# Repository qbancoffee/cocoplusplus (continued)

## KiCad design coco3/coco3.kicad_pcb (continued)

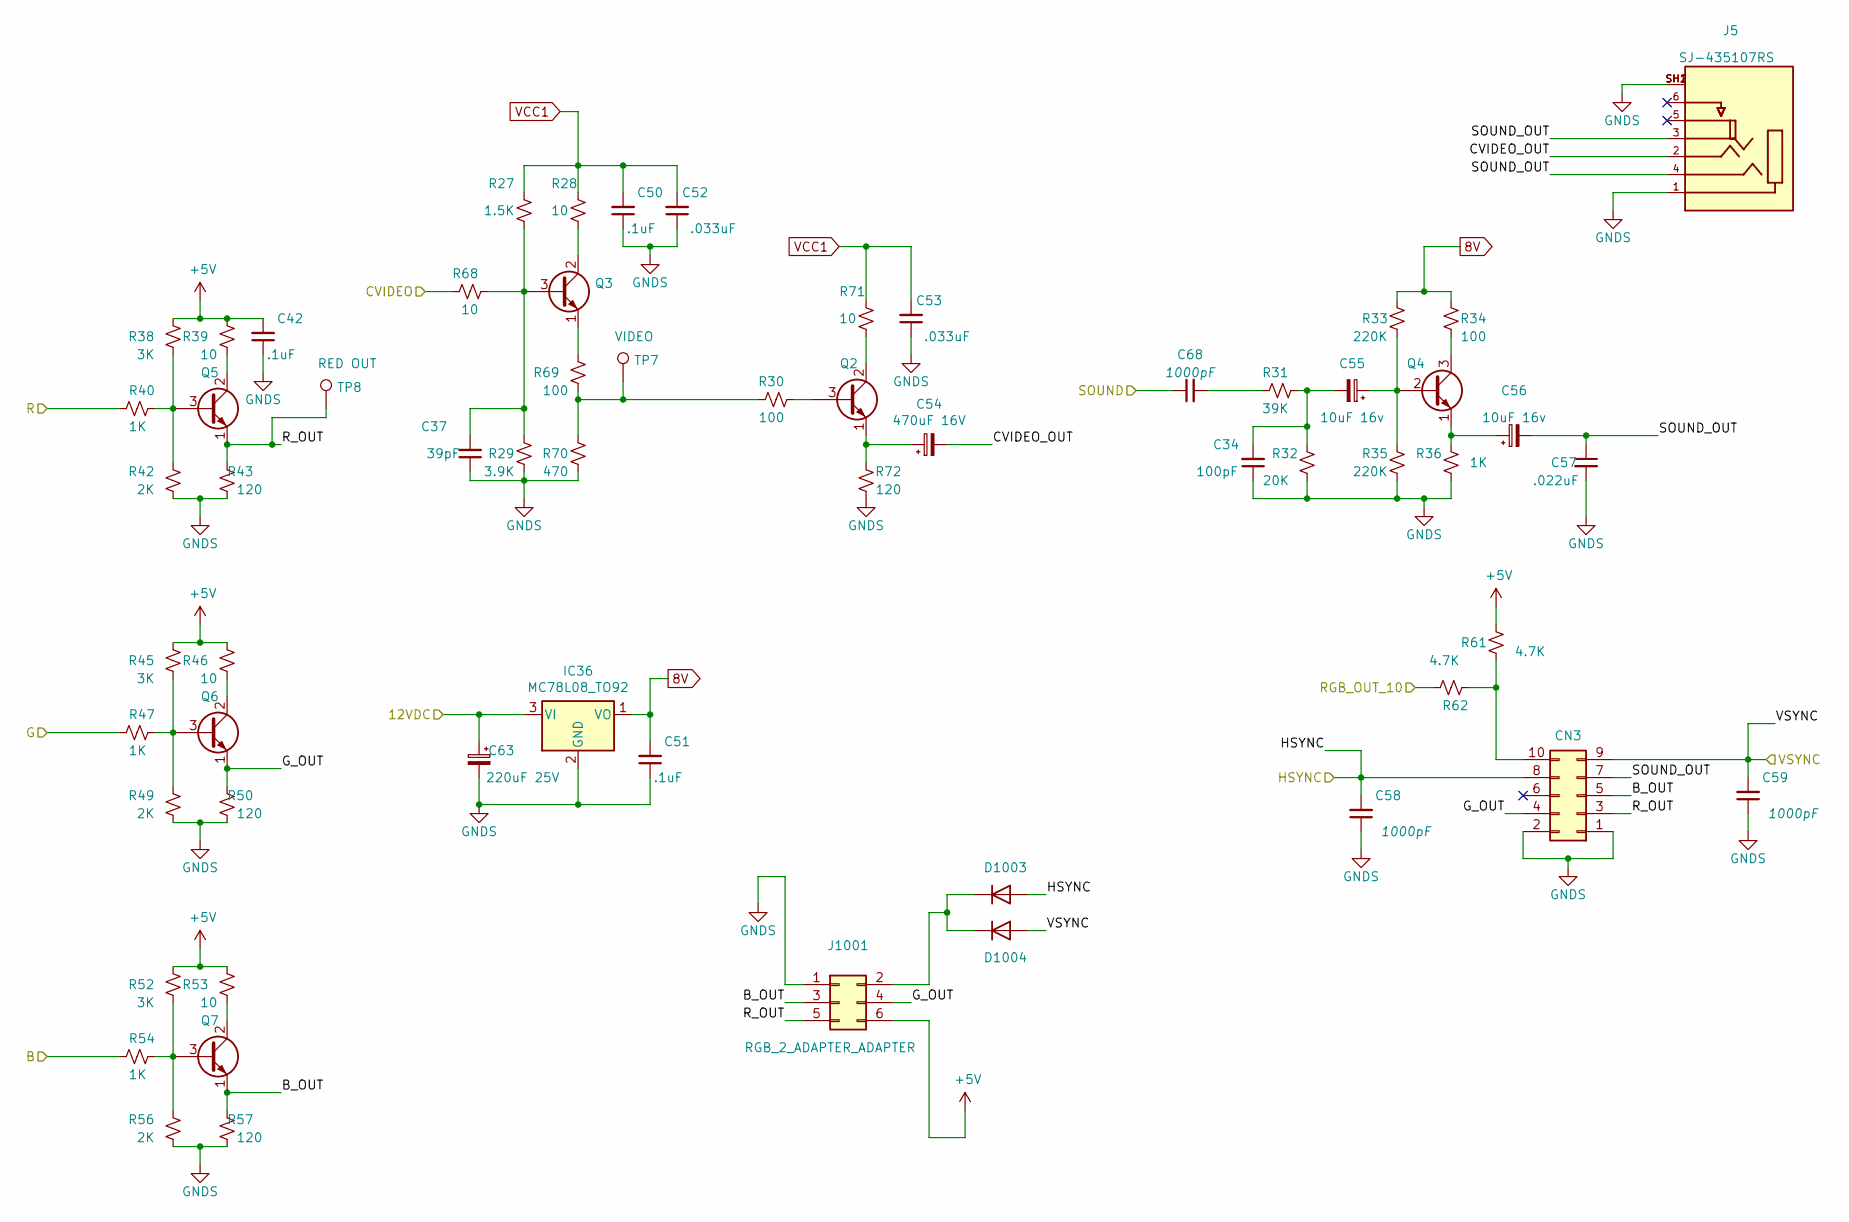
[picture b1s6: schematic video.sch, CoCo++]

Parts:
C34: 100pF; C_0805_2012Metric_Pad1.18x1.45mm_HandSolder; Manufacturer part# CL21C101JBANNNC
C37: 39pF; C_0805_2012Metric_Pad1.18x1.45mm_HandSolder; Manufacturer part# 0805N390J500CT
C42, C50, C51: .1uF; C_0805_2012Metric_Pad1.18x1.45mm_HandSolder; Manufacturer part# CL21A106KAYNNNE
C52, C53: .033uF; C_0805_2012Metric_Pad1.18x1.45mm_HandSolder; Manufacturer part# 0805B333K500NT
C54: 470uF 16V; CP_Elec_8x10; Manufacturer part# VEJ471M1CTR-0810
C55, C56: 10uF 16v; CP_EIA-3216-18_Kemet-A; Manufacturer part# TAJA106K016RNJ
C57: .022uF; C_0805_2012Metric_Pad1.18x1.45mm_HandSolder; Manufacturer part# CL21B223KBANNNC
C58, C59, C68: 1000pF; C_0805_2012Metric_Pad1.18x1.45mm_HandSolder; Manufacturer part# CL21B102KBCNNNC
C63: 220uF 25V; CP_Elec_8x10; Manufacturer part# VEJ221M1ETR-0810
CN3: Conn_02x05_Odd_Even; PinHeader_2x05_P2.54mm_Vertical; Manufacturer part# PRPC005DAAN-RC
D1003, D1004: 1N4148; D_SOD-323F; Manufacturer part# 1N4148WS
IC36: MC78L08_TO92; TO-92_Inline; Manufacturer part# UA78L08ACLPRE3
J5: SJ-435107RS; CUI_SJ-435107RS
J1001: RGB_2_ADAPTER_ADAPTER; PinHeader_2x03_P2.54mm_Horizontal; Manufacturer part# 75867-131LF
Q2, Q3, Q5, Q6, Q7: 2SC945(NTE85); TO-92L_Inline; Manufacturer part# NTE85
Q4: MPSA13(NTE46); TO-92L_Inline; Manufacturer part# NTE46
R27: 1.5K; R_1206_3216Metric_Pad1.30x1.75mm_HandSolder; Manufacturer part# UNI-ROYAL(Uniroyal Elec)
R28, R39, R46, R53, R68, R71: 10; R_1206_3216Metric_Pad1.30x1.75mm_HandSolder; Manufacturer part# 1206W4F100JT5E
R29: 3.9K; R_1206_3216Metric_Pad1.30x1.75mm_HandSolder; Manufacturer part# 1206W4F3901T5E
R30, R34, R69: 100; R_1206_3216Metric_Pad1.30x1.75mm_HandSolder; Manufacturer part# 1206W4F1000T5E
R31: 39K; R_1206_3216Metric_Pad1.30x1.75mm_HandSolder; Manufacturer part# 1206W4F3902T5E
R32: 20K; R_1206_3216Metric_Pad1.30x1.75mm_HandSolder; Manufacturer part# 1206W4F620KT5E
R33, R35: 220K; R_1206_3216Metric_Pad1.30x1.75mm_HandSolder; Manufacturer part# 1206W4F2203T5E
R36, R40, R47, R54: 1K; R_1206_3216Metric_Pad1.30x1.75mm_HandSolder; Manufacturer part# 1206W4F1001T5
R38, R45, R52: 3K; R_1206_3216Metric_Pad1.30x1.75mm_HandSolder; Manufacturer part# 1206W4F3001T5E
R42, R49, R56: 2K; R_1206_3216Metric_Pad1.30x1.75mm_HandSolder; Manufacturer part# 1206W4F2001T5E
R43, R50, R57, R72: 120; R_1206_3216Metric_Pad1.30x1.75mm_HandSolder; Manufacturer part# 1206W4F1200T5E
R61, R62: 4.7K; R_1206_3216Metric_Pad1.30x1.75mm_HandSolder; Manufacturer part# 1206W4F4701T5E
R70: 470; R_1206_3216Metric_Pad1.30x1.75mm_HandSolder; Manufacturer part# 1206W4J0471T5E
TP7: VIDEO; TestPoint_Pad_3.0x3.0mm
TP8: RED OUT; TestPoint_Pad_3.0x3.0mm

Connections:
8V: C51.2, IC36.1 (VO), R33.1, R34.2
+5V: C42.2, J1001.6, R38.2, R39.2, R45.2, R46.2, R52.2, R53.2, R61.1; also elsewhere on the board
/gime/B: R54.2; also elsewhere on the board
/gime/CVIDEO: R68.1; also elsewhere on the board
/gime/G: R47.2; also elsewhere on the board
/gime/HSYNC: C58.2, CN3.8, D1003.2 (A); also elsewhere on the board
/gime/R: R40.2; also elsewhere on the board
/gime/VSYNC: C59.2, CN3.9, D1004.2 (A); also elsewhere on the board
/peripherals/RGB_OUT_10: R62.1; also elsewhere on the board
/peripherals/SOUND: C68.1; also elsewhere on the board
/power/12VDC: C63.1, IC36.3 (VI); also elsewhere on the board
/video/B_OUT: CN3.5, J1001.3, Q7.1 (E), R57.2
/video/CVIDEO_OUT: C54.2, J5.2
/video/G_OUT: CN3.4, J1001.4, Q6.1 (E), R50.2
/video/R_OUT: CN3.3, J1001.5, Q5.1 (E), R43.2, TP8.1
/video/SOUND_OUT: C56.2, C57.1, CN3.7, J5.3, J5.4
unnamed: C34.2, C55.2, R31.2, R32.1
unnamed: C37.2, Q3.3 (B), R27.1, R29.2, R68.2
unnamed: C54.1, Q2.1 (E), R72.2
unnamed: C55.1, Q4.2 (B), R33.2, R35.1
unnamed: C56.1, Q4.1 (E), R36.1
unnamed: C68.2, R31.1
unnamed: CN3.10, R61.2, R62.2
unnamed: D1003.1 (K), D1004.1 (K), J1001.2
unnamed: Q2.2 (C), R71.1
unnamed: Q2.3 (B), R30.2
unnamed: Q3.1 (E), R69.2
unnamed: Q3.2 (C), R28.1
unnamed: Q4.3 (C), R34.1
unnamed: Q5.2 (C), R39.1
unnamed: Q5.3 (B), R38.1, R40.1, R42.2
unnamed: Q6.2 (C), R46.1
unnamed: Q6.3 (B), R45.1, R47.1, R49.2
unnamed: Q7.2 (C), R53.1
unnamed: Q7.3 (B), R52.1, R54.1, R56.2
unnamed: R30.1, R69.1, R70.2, TP7.1
VCC1: C50.2, C52.2, C53.2, R27.2, R28.2, R71.2; also elsewhere on the board

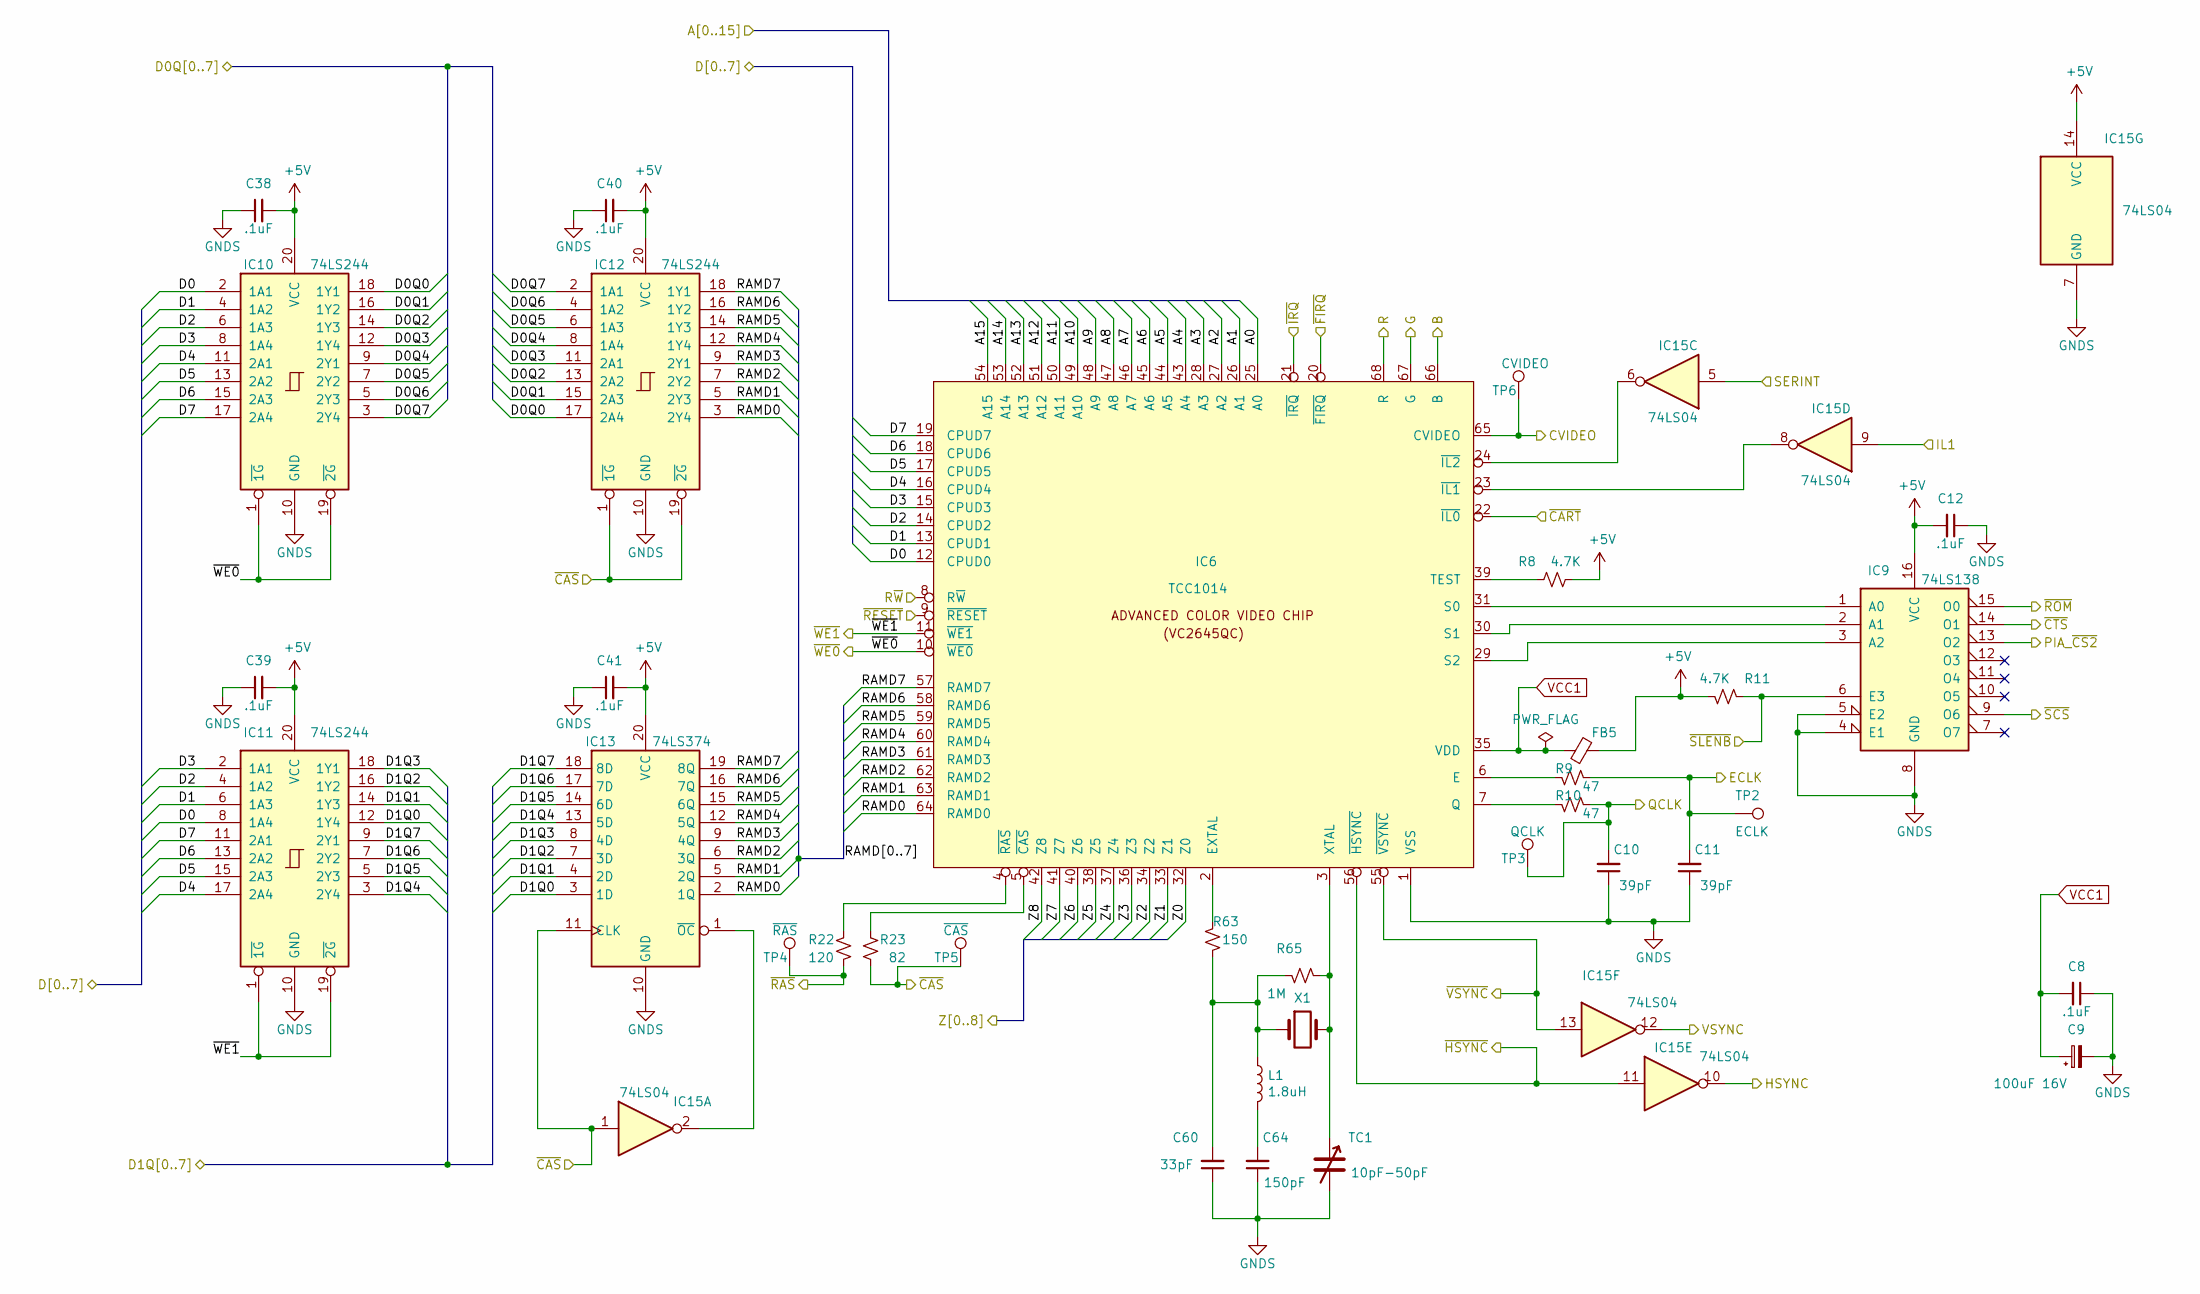
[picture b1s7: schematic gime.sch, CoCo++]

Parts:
C8, C12, C38, C39, C40, C41: .1uF; C_0805_2012Metric_Pad1.18x1.45mm_HandSolder; Manufacturer part# CL21A106KAYNNNE
C9: 100uF 16V; CP_Elec_6.3x5.3; Manufacturer part# VEJ101M1CTR-0605
C10, C11: 39pF; C_0805_2012Metric_Pad1.18x1.45mm_HandSolder; Manufacturer part# 0805N390J500CT
C60: 33pF; C_0805_2012Metric_Pad1.18x1.45mm_HandSolder; Manufacturer part# CL21C330JBANNNC
C64: 150pF; C_0805_2012Metric_Pad1.18x1.45mm_HandSolder; Manufacturer part# 0805B151K500NT
FB5: FB_28L0138-10R-10; Manufacturer part# 28L0138-10R-10
IC6: TCC1014; PLCC-68_THT-Socket; Manufacturer part# A-CCS 068-G-T
IC9: 74LS138; SOP-16_3.9x9.9mm_P1.27mm; Manufacturer part# XL74LS138
IC10, IC11, IC12: 74LS244; SOIC-20W_7.5x12.8mm_P1.27mm; Manufacturer part# SN74LS244DWR
IC13: 74LS374; SOIC-20W_7.5x12.8mm_P1.27mm; Manufacturer part# SN74LS374NSR
IC15: 74LS04; SOIC-14_3.9x8.7mm_P1.27mm; Manufacturer part# SN74LS04DR
L1: 1.8uH; L_Axial_L9.5mm_D4.0mm_P12.70mm_Horizontal_Fastron_SMCC; Manufacturer part# 1537-18K
R8, R11: 4.7K; R_1206_3216Metric_Pad1.30x1.75mm_HandSolder; Manufacturer part# 1206W4F4701T5E
R9, R10: 47; R_1206_3216Metric_Pad1.30x1.75mm_HandSolder; Manufacturer part# 1206W4J0470T5E
R22: 120; R_1206_3216Metric_Pad1.30x1.75mm_HandSolder; Manufacturer part# 1206W4F1200T5E
R23: 82; R_1206_3216Metric_Pad1.30x1.75mm_HandSolder; Manufacturer part# 1206W4F820JT5E
R63: 150; R_1206_3216Metric_Pad1.30x1.75mm_HandSolder; Manufacturer part# 1206W4F1500T5E
R65: 1M; R_1206_3216Metric_Pad1.30x1.75mm_HandSolder; Manufacturer part# 1206W4F1004T5E
TC1: 10pF-50pF; C_Rect_L7.2mm_W7.2mm_P5.00mm_FKS2_FKP2_MKS2_MKP2; Manufacturer part# GKG60015
TP2: ECLK; TestPoint_Pad_3.0x3.0mm
TP3: QCLK; TestPoint_Pad_3.0x3.0mm
TP4: ~RAS; TestPoint_Pad_3.0x3.0mm
TP5: ~CAS; TestPoint_Pad_3.0x3.0mm
TP6: CVIDEO; TestPoint_Pad_3.0x3.0mm
X1: 28.63636 MHz; XTAL_ECS-286.3-20-46X; Manufacturer part# ECS-286.3-20-46X

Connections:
+5V: C12.2, C38.2, C39.2, C40.2, C41.2, FB5.2, IC9.16 (VCC), IC10.20 (VCC), IC11.20 (VCC), IC12.20 (VCC), IC13.20 (VCC), IC15.14 (VCC), R8.2, R11.2; also elsewhere on the board
/A0: IC6.25 (A0); also elsewhere on the board
/A1: IC6.26 (A1); also elsewhere on the board
/A2: IC6.27 (A2); also elsewhere on the board
/A3: IC6.28 (A3); also elsewhere on the board
/A4: IC6.43 (A4); also elsewhere on the board
/A5: IC6.44 (A5); also elsewhere on the board
/A6: IC6.45 (A6); also elsewhere on the board
/A7: IC6.46 (A7); also elsewhere on the board
/A8: IC6.47 (A8); also elsewhere on the board
/A9: IC6.48 (A9); also elsewhere on the board
/A10: IC6.49 (A10); also elsewhere on the board
/A11: IC6.50 (A11); also elsewhere on the board
/A12: IC6.51 (A12); also elsewhere on the board
/A13: IC6.52 (A13); also elsewhere on the board
/A14: IC6.53 (A14); also elsewhere on the board
/A15: IC6.54 (A15); also elsewhere on the board
/D0: IC6.12 (CPUD0), IC10.2 (1A1), IC11.8 (1A4); also elsewhere on the board
/D1: IC6.13 (CPUD1), IC10.4 (1A2), IC11.6 (1A3); also elsewhere on the board
/D2: IC6.14 (CPUD2), IC10.6 (1A3), IC11.4 (1A2); also elsewhere on the board
/D3: IC6.15 (CPUD3), IC10.8 (1A4), IC11.2 (1A1); also elsewhere on the board
/D4: IC6.16 (CPUD4), IC10.11 (2A1), IC11.17 (2A4); also elsewhere on the board
/D5: IC6.17 (CPUD5), IC10.13 (2A2), IC11.15 (2A3); also elsewhere on the board
/D6: IC6.18 (CPUD6), IC10.15 (2A3), IC11.13 (2A2); also elsewhere on the board
/D7: IC6.19 (CPUD7), IC10.17 (2A4), IC11.11 (2A1); also elsewhere on the board
/ECLK: C11.2, R9.1, TP2.1; also elsewhere on the board
/QCLK: C10.2, R10.1, TP3.1; also elsewhere on the board
/R~W: IC6.8 (R~W); also elsewhere on the board
/dram/D0Q0: IC10.18 (1Y1), IC12.17 (2A4); also elsewhere on the board
/dram/D0Q1: IC10.16 (1Y2), IC12.15 (2A3); also elsewhere on the board
/dram/D0Q2: IC10.14 (1Y3), IC12.13 (2A2); also elsewhere on the board
/dram/D0Q3: IC10.12 (1Y4), IC12.11 (2A1); also elsewhere on the board
/dram/D0Q4: IC10.9 (2Y1), IC12.8 (1A4); also elsewhere on the board
/dram/D0Q5: IC10.7 (2Y2), IC12.6 (1A3); also elsewhere on the board
/dram/D0Q6: IC10.5 (2Y3), IC12.4 (1A2); also elsewhere on the board
/dram/D0Q7: IC10.3 (2Y4), IC12.2 (1A1); also elsewhere on the board
/dram/D1Q0: IC11.12 (1Y4), IC13.3 (1D); also elsewhere on the board
/dram/D1Q1: IC11.14 (1Y3), IC13.4 (2D); also elsewhere on the board
/dram/D1Q2: IC11.16 (1Y2), IC13.7 (3D); also elsewhere on the board
/dram/D1Q3: IC11.18 (1Y1), IC13.8 (4D); also elsewhere on the board
/dram/D1Q4: IC11.3 (2Y4), IC13.13 (5D); also elsewhere on the board
/dram/D1Q5: IC11.5 (2Y3), IC13.14 (6D); also elsewhere on the board
/dram/D1Q6: IC11.7 (2Y2), IC13.17 (7D); also elsewhere on the board
/dram/D1Q7: IC11.9 (2Y1), IC13.18 (8D); also elsewhere on the board
/dram/Z0: IC6.32 (Z0); also elsewhere on the board
/dram/Z1: IC6.33 (Z1); also elsewhere on the board
/dram/Z2: IC6.34 (Z2); also elsewhere on the board
/dram/Z3: IC6.36 (Z3); also elsewhere on the board
/dram/Z4: IC6.37 (Z4); also elsewhere on the board
/dram/Z5: IC6.38 (Z5); also elsewhere on the board
/dram/Z6: IC6.40 (Z6); also elsewhere on the board
/dram/Z7: IC6.41 (Z7); also elsewhere on the board
/dram/Z8: IC6.42 (Z8); also elsewhere on the board
/dram/~CAS: IC12.1 (~1G), IC12.19 (~2G), IC13.11 (CLK), IC15.1, R23.1, TP5.1; also elsewhere on the board
/dram/~RAS: R22.1, TP4.1; also elsewhere on the board
/dram/~WE0: IC6.10 (~WE0), IC10.1 (~1G), IC10.19 (~2G); also elsewhere on the board
/dram/~WE1: IC6.11 (~WE1), IC11.1 (~1G), IC11.19 (~2G); also elsewhere on the board
/gime/B: IC6.66 (B); also elsewhere on the board
/gime/CVIDEO: IC6.65 (CVIDEO), TP6.1; also elsewhere on the board
/gime/G: IC6.67 (G); also elsewhere on the board
/gime/HSYNC: IC15.10; also elsewhere on the board
/gime/IL1: IC15.9; also elsewhere on the board
/gime/PIA_~CS2: IC9.13 (O2); also elsewhere on the board
/gime/R: IC6.68 (R); also elsewhere on the board
/gime/RAMD0: IC6.64 (RAMD0), IC12.3 (2Y4), IC13.2 (1Q)
/gime/RAMD1: IC6.63 (RAMD1), IC12.5 (2Y3), IC13.5 (2Q)
/gime/RAMD2: IC6.62 (RAMD2), IC12.7 (2Y2), IC13.6 (3Q)
/gime/RAMD3: IC6.61 (RAMD3), IC12.9 (2Y1), IC13.9 (4Q)
/gime/RAMD4: IC6.60 (RAMD4), IC12.12 (1Y4), IC13.12 (5Q)
/gime/RAMD5: IC6.59 (RAMD5), IC12.14 (1Y3), IC13.15 (6Q)
/gime/RAMD6: IC6.58 (RAMD6), IC12.16 (1Y2), IC13.16 (7Q)
/gime/RAMD7: IC6.57 (RAMD7), IC12.18 (1Y1), IC13.19 (8Q)
/gime/SERINT: IC15.5; also elsewhere on the board
/gime/VSYNC: IC15.12; also elsewhere on the board
/gime/~HSYNC: IC6.56 (~HSYNC), IC15.11; also elsewhere on the board
/gime/~ROM: IC9.15 (O0); also elsewhere on the board
/gime/~VSYNC: IC6.55 (~VSYNC), IC15.13; also elsewhere on the board
/~CART: IC6.22 (~IL0); also elsewhere on the board
/~CTS: IC9.14 (O1); also elsewhere on the board
/~FIRQ: IC6.20 (~FIRQ); also elsewhere on the board
/~IRQ: IC6.21 (~IRQ); also elsewhere on the board
/~RESET: IC6.9 (~RESET); also elsewhere on the board
/~SCS: IC9.9 (O6); also elsewhere on the board
/~SLENB: IC9.6 (E3), R11.1; also elsewhere on the board
unnamed: C60.2, L1.1, R63.2, R65.2, X1.1
unnamed: C64.2, L1.2
unnamed: IC6.2 (EXTAL), R63.1
unnamed: IC6.3 (XTAL), R65.1, TC1.1, X1.2
unnamed: IC6.4 (~RAS), R22.2
unnamed: IC6.5 (~CAS), R23.2
unnamed: IC6.6 (E), R9.2
unnamed: IC6.7 (Q), R10.2
unnamed: IC6.29 (S2), IC9.3 (A2)
unnamed: IC6.30 (S1), IC9.2 (A1)
unnamed: IC6.31 (S0), IC9.1 (A0)
unnamed: IC6.39 (TEST), R8.1
unnamed: IC13.1 (~OC), IC15.2
unnamed: IC6.24 (~IL2), IC15.6
unnamed: IC6.23 (~IL1), IC15.8
VCC1: C8.2, C9.1, FB5.1, IC6.35 (VDD); also elsewhere on the board

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
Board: 2 copper layers, 211 parts (1 on the bottom side), 222 nets, no tracks yet.

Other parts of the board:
C30: 20pF; C_0805_2012Metric_Pad1.18x1.45mm_HandSolder
R15: 100K; R_0603_1608Metric_Pad0.98x0.95mm_HandSolder
R16: 330K; R_0805_2012Metric_Pad1.20x1.40mm_HandSolder
R17: 160K; R_0603_1608Metric_Pad0.98x0.95mm_HandSolder
R18, R19: 82K; R_0805_2012Metric_Pad1.20x1.40mm_HandSolder
R20: 40.2K; R_0603_1608Metric_Pad0.98x0.95mm_HandSolder
R25: 300K; R_0805_2012Metric_Pad1.20x1.40mm_HandSolder
R26: 20K; R_0805_2012Metric_Pad1.20x1.40mm_HandSolder
R37, R41: 10K; R_0805_2012Metric_Pad1.20x1.40mm_HandSolder
R44: 10M; R_0805_2012Metric_Pad1.20x1.40mm_HandSolder
R48: 1K; R_0805_2012Metric_Pad1.20x1.40mm_HandSolder
U1: 74LS367; SOIC-16_3.9x9.9mm_P1.27mm
U2: TS5A3166DBVR; SOT-23-5
U3: LM393; TSSOP-8_4.4x3mm_P0.65mm
U4: CD4052B; HTSSOP-16-1EP_4.4x5mm_P0.65mm_EP3x3mm

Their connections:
+5V: R15.2, R48.2, U1.16, U2.5, U3.8, U4.16; also elsewhere on the board
/SND_IN_2: U4.15; also elsewhere on the board
/peripherals/CASS_DATA_IN_TTL: U3.7; also elsewhere on the board
/peripherals/Color Computer DAC/CASSETTE_OUT: C30.1, R15.1, R16.1, R17.1, R18.2, R19.1, R20.1, R26.1, R37.1, U3.2; also elsewhere on the board
/peripherals/Color Computer DAC/CASSETTE_SND_IN: U4.14; also elsewhere on the board
/peripherals/Color Computer DAC/D0: U1.2; also elsewhere on the board
/peripherals/Color Computer DAC/D1: U1.4; also elsewhere on the board
/peripherals/Color Computer DAC/D2: U1.6; also elsewhere on the board
/peripherals/Color Computer DAC/D3: U1.10; also elsewhere on the board
/peripherals/Color Computer DAC/D4: U1.12; also elsewhere on the board
/peripherals/Color Computer DAC/D5: U1.14; also elsewhere on the board
/peripherals/Color Computer DAC/DAC_OUT: R18.1, R25.2, U4.12
/peripherals/Color Computer DAC/SND_ENABLE: U2.4; also elsewhere on the board
/peripherals/JOY0: U4.1; also elsewhere on the board
/peripherals/JOY1: U4.5; also elsewhere on the board
/peripherals/JOY2: U4.2; also elsewhere on the board
/peripherals/JOY3: U4.4; also elsewhere on the board
/peripherals/PA7: R44.1, R48.1, U3.1; also elsewhere on the board
/peripherals/SELA: U4.10; also elsewhere on the board
/peripherals/SELB: U4.9; also elsewhere on the board
/peripherals/SOUND: U2.2; also elsewhere on the board
unnamed: R16.2, U1.3
unnamed: R17.2, U1.5
unnamed: R19.2, U1.7
unnamed: R20.2, U1.9
unnamed: R26.2, U1.11
unnamed: R37.2, U1.13
unnamed: R41.1, R44.2, U3.3
unnamed: R41.2, U4.3
unnamed 216: U3.5; also elsewhere on the board
unnamed 217: U3.6; also elsewhere on the board
unnamed: U2.1, U4.13

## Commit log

2021-08-31 Create README.md
    initial file
2021-08-31 changed title
2021-08-31 changed title to CoCo++ and changed revision to 1.0.0
2021-08-31 added license file from the bit-preserve project
2021-09-02 -replaced PIA's with he PLCC44 package versions -removed RF modulator -removed DRAM
2021-09-03 -repplaced a whole bunch of THT components with SMT components
2021-09-04 -converted more components from THT to SMD -replaced SALT chip with replacement circuitry
2021-09-12 routed the board
2021-12-10 added replacement circuitry for SC77526P DAC/ADC chip
2021-12-10 cleaned up some components
2021-12-10 removed autosave files
